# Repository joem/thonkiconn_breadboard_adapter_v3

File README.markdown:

Thonkiconn Breadboard Adapter V3
================================

My second attempt at a breadboard adapter for using "Thonkiconn"-style 3.5mm mono jacks. These jacks _can_ plug directly into a breadboard but they’re not very secure, so a breadboard adapter with more pins is a nice way to secure it. Also I tend to forget which pin is which when using other adapters that I’ve found. Sometimes I use the jack board from Mutable Instrument's Breadboard Friends, but other times the connections to the rails are not what I want, or I don't want to use both sides of the breadboard.

This is mostly based on [little-scale’s similar board](http://little-scale.blogspot.com/2017/11/thonkiconn-breadboard-adapter-for.html) but I wanted a smaller board and labels for the connections.

:information_source: _Note: The grounds are not connected to each other on the board. I did it this way so that you can pass two wildly different signals through the jacks independently if desired. (In truth, there probably aren't very many use cases where this is necessary.)_

This was designed as a KiCad project, but if you want to fabricate a PCB you don't need KiCad since the gerbers are in the [gerbers folder](gerbers/). Also, there's a PDF schematic in the [pdfs directory](pdfs/) though it's very simple. And if you just want to order PCBs, [there's an OSHPark project of the previous, nearly-identical version](https://oshpark.com/shared_projects/N9XmX8cB) (the traces were in a different place and a little thinner on the older board).

Opening the KiCad project requires KiCad 6 at a minimum. I've removed the old KiCad 5 files.

## BOM:

- (2) "Thonkiconn"-style 3.5mm mono jacks (QingPu WQP-WQP518MA or WQP-PJ398SM or WQP-PJ301M-12, or compatible)
- (2) 2x3 pin male headers

## Render from KiCad:

------

Update 2020/04/17: This board has been tested and works great.

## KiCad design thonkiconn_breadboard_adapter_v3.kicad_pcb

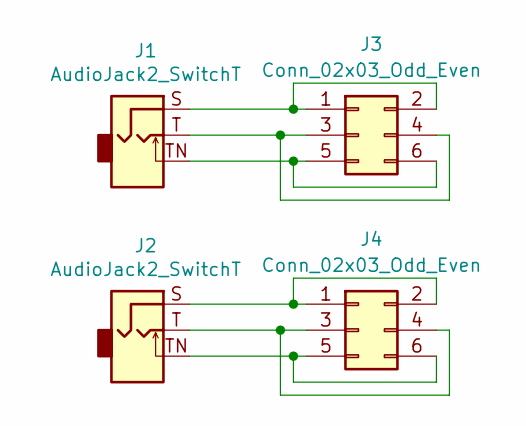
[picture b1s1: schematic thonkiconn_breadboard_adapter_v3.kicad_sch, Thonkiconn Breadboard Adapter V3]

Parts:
J1, J2: AudioJack2_SwitchT; Jack_3.5mm_QingPu_WQP-PJ398SM_Vertical_CircularHoles
J3, J4: Conn_02x03_Odd_Even; PinHeader_2x03_P2.54mm_Vertical

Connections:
unnamed: J1.S, J3.1, J3.2
unnamed: J1.T, J3.3, J3.4
unnamed: J1.TN, J3.5, J3.6
unnamed: J2.S, J4.1, J4.2
unnamed: J2.T, J4.3, J4.4
unnamed: J2.TN, J4.5, J4.6

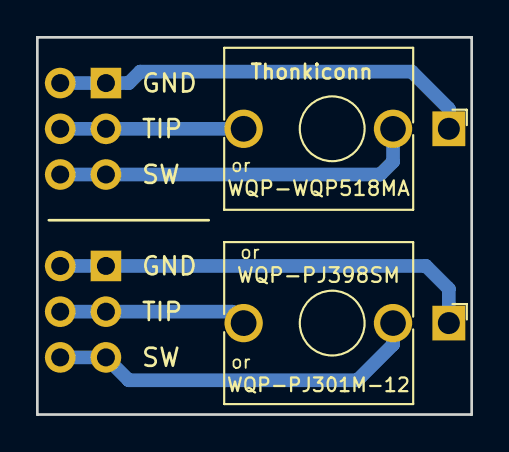
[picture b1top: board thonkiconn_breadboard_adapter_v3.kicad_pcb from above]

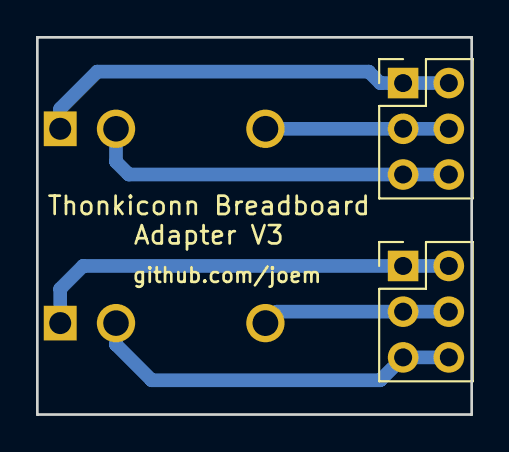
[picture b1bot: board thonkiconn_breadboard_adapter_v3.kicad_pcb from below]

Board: 2 copper layers, 24.1 x 21.0 mm, 4 parts (2 on the bottom side), 6 nets.

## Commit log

2020-04-09 Rename project files, minorly
2020-04-09 Add gerbers, images, and pdfs
2020-04-09 Add readme
2020-04-19 Update readme to reflect successful test
2020-04-22 Update silkscreen with github URL
2023-04-02 Update project to kicad 6+
2023-04-02 Update .gitignore to ignore kicad 6 temp files
